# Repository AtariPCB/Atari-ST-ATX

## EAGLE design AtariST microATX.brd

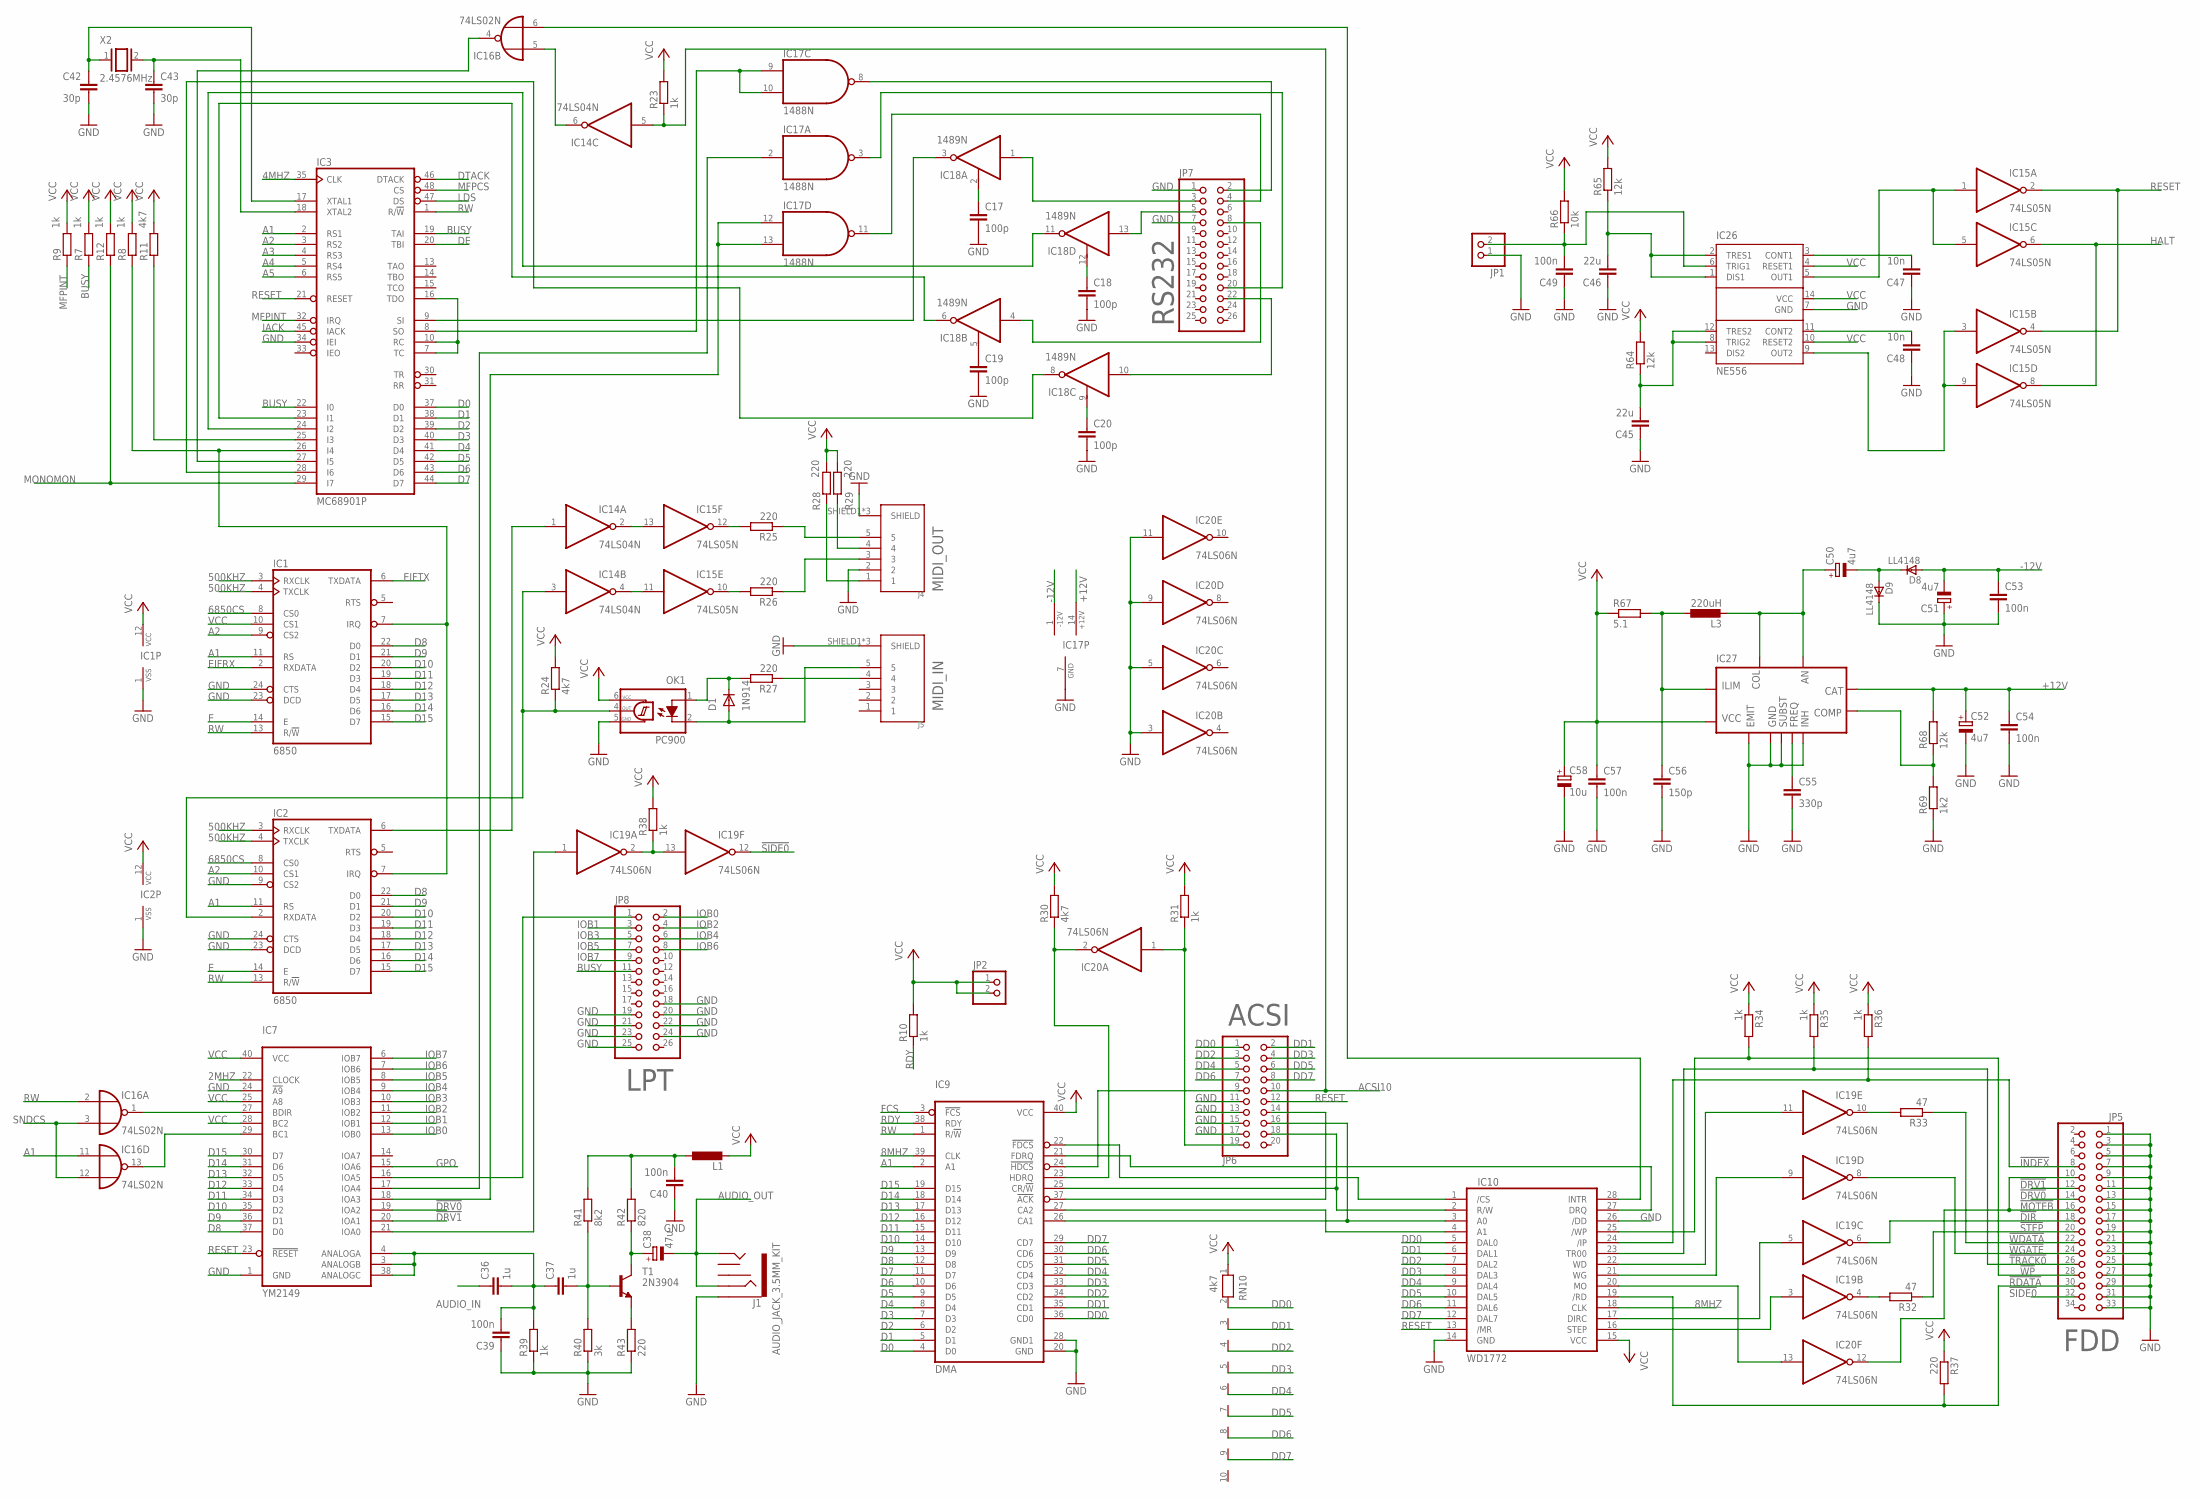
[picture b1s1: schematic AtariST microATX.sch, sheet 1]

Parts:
C17, C18, C19, C20: 100p; C0805
C36, C37: 1u; C0805
C38: 47u; E2-5
C39, C40, C49, C53, C54, C57: 100n; C0805
C42, C43: 30p; C0805
C45, C46: 22u; C1206
C47, C48: 10n; C0805
C50, C51, C52: 4u7; E2-5
C55: 330p; C0805
C56: 150p; C0805
C58: 10u; E2-5
D1: 1N914; DO35-10
D8, D9: LL4148; SOD80_DO213AA_MINIMELF
IC1, IC2: 6850; DIL24
IC3: MC68901P; DIL48
IC7: YM2149; DIL40
IC9: DMA; DIL40
IC10: WD1772; DIL28
IC14: 74LS04N; DIL14
IC15: 74LS05N; DIL14
IC16: 74LS02N; DIL14
IC17: 1488N; DIL14
IC18: 1489N; DIL14
IC19, IC20: 74LS06N; DIL14
IC26: NE556; DIL14
IC27: TL497; DIL14
J1: AUDIO_JACK_3.5MM_KIT; AUDIO-JACK-KIT
J4: MIDI_OUT; DIN5
J5: MIDI_IN; DIN5
JP1, JP2: PINHD-1X2; 1X02
JP5: PINHD-2X17; 2X17
JP6: PINHD-2X10; 2X10
JP7: RS232; 2X13
JP8: LPT; 2X13
L1: L-EU0204/7; 0204/7
L3: 220uH; 0204/7
OK1: PC900; DIL06
R7, R8, R9, R10, R12, R23, R31, R34, R35, R36, R38, R39: 1k; R0805
R11, R24, R30: 4k7; R0805
R25, R26, R27, R28, R29, R37, R43: 220; R0805
R32, R33: 47; 0204/5
R40: 3k; R0805
R41: 8k2; R0805
R42: 820; R0805
R64, R65, R68: 12k; R0805
R66: 10k; R0805
R67: 5.1; 0204/7
R69: 1k2; R0805
RN10: 4k7; RN-10
T1: 2N3904; TO92
X2: 2.4576MHz; QS

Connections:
2: J5.2
2MHZ: IC7.22 (CLOCK); also elsewhere on the board
4MHZ: IC3.35 (CLK); also elsewhere on the board
8MHZ: IC9.39 (CLK), IC10.18 (CLK); also elsewhere on the board
500KHZ: IC1.3 (RXCLK), IC1.4 (TXCLK), IC2.3 (RXCLK), IC2.4 (TXCLK); also elsewhere on the board
6850CS: IC1.8 (CS0), IC2.8 (CS0); also elsewhere on the board
!DIR: IC19.6 (O), JP5.18
!DRV0: IC7.19 (IOA2), JP5.14
!DRV1: IC7.20 (IOA1), JP5.12
!INDEX: IC10.24 (/IP), JP5.8, R36.2
!MOTEB: IC20.12 (O), JP5.10, JP5.16
!RDATA: IC10.19 (/RD), JP5.30, R37.2
!SIDE0: IC19.12 (O), JP5.32
!STEP: JP5.20, R32.1
!TRACK0: IC10.23 (TR00), JP5.26, R35.2
!WDATA: JP5.22, R33.1
!WGATE: IC19.8 (O), JP5.24
!WP: IC10.25 (/WP), JP5.28, R34.2
+12V: C52.+, C54.1, IC17.14 (+12V), IC27.6 (CAT), R68.2; also elsewhere on the board
-12V: C51.-, C53.1, D8.A, IC17.1 (-12V)
A1: IC1.11 (RS), IC2.11 (RS), IC3.2 (RS1), IC9.2 (A1), IC16.11 (I0); also elsewhere on the board
A2: IC1.9 (CS2), IC2.10 (CS1), IC3.3 (RS2); also elsewhere on the board
A3: IC3.4 (RS3); also elsewhere on the board
A4: IC3.5 (RS4); also elsewhere on the board
A5: IC3.6 (RS5); also elsewhere on the board
ACSI10: IC14.5 (I), JP6.10, R23.1; also elsewhere on the board
AUDIO_IN: C36.1; also elsewhere on the board
AUDIO_OUT: C38.-, J1.RING, J1.TIP; also elsewhere on the board
BUSY: IC3.19 (TAI), IC3.22 (I0), JP8.11, R7.1
D0: IC3.37 (D0), IC9.4 (D0); also elsewhere on the board
D1: IC3.38 (D1), IC9.5 (D1); also elsewhere on the board
D2: IC3.39 (D2), IC9.6 (D2); also elsewhere on the board
D3: IC3.40 (D3), IC9.7 (D3); also elsewhere on the board
D4: IC3.41 (D4), IC9.8 (D4); also elsewhere on the board
D5: IC3.42 (D5), IC9.9 (D5); also elsewhere on the board
D6: IC3.43 (D6), IC9.10 (D6); also elsewhere on the board
D7: IC3.44 (D7), IC9.11 (D7); also elsewhere on the board
D8: IC1.22 (D0), IC2.22 (D0), IC7.37 (D0), IC9.12 (D8); also elsewhere on the board
D9: IC1.21 (D1), IC2.21 (D1), IC7.36 (D1), IC9.13 (D9); also elsewhere on the board
D10: IC1.20 (D2), IC2.20 (D2), IC7.35 (D2), IC9.14 (D10); also elsewhere on the board
D11: IC1.19 (D3), IC2.19 (D3), IC7.34 (D3), IC9.15 (D11); also elsewhere on the board
D12: IC1.18 (D4), IC2.18 (D4), IC7.33 (D4), IC9.16 (D12); also elsewhere on the board
D13: IC1.17 (D5), IC2.17 (D5), IC7.32 (D5), IC9.17 (D13); also elsewhere on the board
D14: IC1.16 (D6), IC2.16 (D6), IC7.31 (D6), IC9.18 (D14); also elsewhere on the board
D15: IC1.15 (D7), IC2.15 (D7), IC7.30 (D7), IC9.19 (D15); also elsewhere on the board
DD0: IC9.36 (CD0), IC10.5 (DAL0), JP6.1, RN10.2
DD1: IC9.35 (CD1), IC10.6 (DAL1), JP6.2, RN10.3
DD2: IC9.34 (CD2), IC10.7 (DAL2), JP6.3, RN10.4
DD3: IC9.33 (CD3), IC10.8 (DAL3), JP6.4, RN10.5
DD4: IC9.32 (CD4), IC10.9 (DAL4), JP6.5, RN10.6
DD5: IC9.31 (CD5), IC10.10 (DAL5), JP6.6, RN10.7
DD6: IC9.30 (CD6), IC10.11 (DAL6), JP6.7, RN10.8
DD7: IC9.29 (CD7), IC10.12 (DAL7), JP6.8, RN10.9
DE: IC3.20 (TBI); also elsewhere on the board
DTACK: IC3.46 (DTACK); also elsewhere on the board
E: IC1.14 (E), IC2.14 (E); also elsewhere on the board
EIFRX: IC1.2 (RXDATA); also elsewhere on the board
EIFTX: IC1.6 (TXDATA); also elsewhere on the board
FCS: IC9.3 (!FCS); also elsewhere on the board
GND: C17.2, C18.2, C19.2, C20.2, C39.1, C40.1, C42.2, C43.2, C45.1, C46.1, C47.1, C48.1, C49.1, C51.+, C52.-, C53.2, C54.2, C55.2, C56.2, C57.2, C58.-, D9.C, IC1.1 (VSS), IC1.23 (DCD), IC1.24 (CTS), IC2.1 (VSS), IC2.9 (CS2), IC2.23 (DCD), IC2.24 (CTS), IC3.34 (IEI), IC3.36 (GND), IC7.1 (GND), IC7.24 (!A9), IC9.20 (GND), IC9.28 (GND1), IC10.14 (GND), IC10.26 (/DD), IC14.7 (GND), IC15.7 (GND), IC16.7 (GND), IC17.7 (GND), IC18.7 (GND), IC19.7 (GND), IC20.3 (I), IC20.5 (I), IC20.7 (GND), IC20.9 (I), IC20.11 (I), IC26.7 (GND), IC27.2 (INH), IC27.4 (SUBST), IC27.5 (GND), IC27.8 (EMIT), J1.SLEEVE, J4.2, J4.SHIELD1 (SHIELD), J4.SHIELD2 (SHIELD), J4.SHIELD3 (SHIELD), J5.SHIELD1 (SHIELD), J5.SHIELD2 (SHIELD), J5.SHIELD3 (SHIELD), JP1.1, JP5.1, JP5.3, JP5.5, JP5.7, JP5.9, JP5.11, JP5.13, JP5.15, JP5.17, JP5.19, JP5.21, JP5.23, JP5.25, JP5.27, JP5.29, JP5.31, JP5.33, JP6.11, JP6.13, JP6.15, JP6.17, JP7.1, JP7.7, JP8.18, JP8.19, JP8.20, JP8.21, JP8.22, JP8.23, JP8.24, JP8.25, OK1.5 (GND), R39.1, R40.1, R43.1, R69.1; also elsewhere on the board
GPO: IC7.15 (IOA6); also elsewhere on the board
HALT: IC15.6 (O), IC15.8 (O); also elsewhere on the board
IACK: IC3.45 (IACK); also elsewhere on the board
IOB0: IC7.13 (IOB0), JP8.2
IOB1: IC7.12 (IOB1), JP8.3
IOB2: IC7.11 (IOB2), JP8.4
IOB3: IC7.10 (IOB3), JP8.5
IOB4: IC7.9 (IOB4), JP8.6
IOB5: IC7.8 (IOB5), JP8.7
IOB6: IC7.7 (IOB6), JP8.8
IOB7: IC7.6 (IOB7), JP8.9
LDS: IC3.47 (DS); also elsewhere on the board
MFPCS: IC3.48 (CS); also elsewhere on the board
MFPINT: IC3.32 (IRQ), R9.1; also elsewhere on the board
MONOMON: IC3.29 (I7), R12.1; also elsewhere on the board
unnamed: C48.2, IC26.11 (CONT2)
unnamed: IC7.16 (IOA5), JP8.1
unnamed: IC7.27 (BDIR), IC16.1 (O)
unnamed: IC7.29 (BC1), IC16.13 (O)
unnamed: IC1.7 (IRQ), IC2.7 (IRQ), IC3.26 (I4), R8.1
unnamed: IC3.7 (TC), IC3.10 (RC), IC3.16 (TDO)
unnamed: IC3.9 (SI), IC18.3 (O)
unnamed: IC3.8 (SO), IC17.9 (I0), IC17.10 (I1)
unnamed: IC3.25 (I3), R11.1
unnamed: IC17.8 (O), JP7.2
unnamed: IC18.1 (I), JP7.3
unnamed: IC17.11 (O), JP7.4
unnamed: IC18.13 (I), JP7.5
unnamed: IC18.4 (I), JP7.8
unnamed: IC18.10 (I), JP7.22
unnamed: IC17.3 (O), JP7.20
unnamed: C19.1, IC18.5 (RC)
unnamed: C20.1, IC18.9 (RC)
unnamed: C18.1, IC18.12 (RC)
unnamed: C17.1, IC18.2 (RC)
unnamed: IC3.24 (I2), IC18.11 (O)
unnamed: IC3.23 (I1), IC18.6 (O)
unnamed: IC3.28 (I6), IC18.8 (O)
unnamed: IC7.17 (IOA4), IC17.2 (I)
unnamed: IC7.18 (IOA3), IC17.12 (I0), IC17.13 (I1)
unnamed: IC10.28 (INTR), IC16.6 (I1)
unnamed: IC14.6 (O), IC16.5 (I0)
unnamed: IC3.27 (I5), IC16.4 (O)
unnamed: IC2.6 (TXDATA), IC14.1 (I)
unnamed: IC2.2 (RXDATA), IC14.3 (I), OK1.4 (OUT), R24.1
unnamed: IC14.2 (O), IC15.13 (I)
unnamed: IC14.4 (O), IC15.11 (I)
unnamed: J4.1, R28.1
unnamed: J4.4, R29.1
unnamed: IC9.26 (CA1), IC10.3 (A0), JP6.16
unnamed: J4.5, R25.1
unnamed: J4.3, R26.1
unnamed: IC15.10 (O), R26.2
unnamed: IC15.12 (O), R25.2
unnamed: J5.4, R27.1
unnamed: D1.C, OK1.1 (A), R27.2
unnamed: D1.A, J5.5, OK1.2 (C)
unnamed: IC9.27 (CA2), IC10.4 (A1)
unnamed: IC9.25 (CR/!W), IC10.2 (R/W), JP6.18
unnamed: IC9.22 (!FDCS), IC10.1 (/CS)
unnamed: IC9.21 (FDRQ), IC10.27 (DRQ)
unnamed: IC9.24 (!HDCS), JP6.9
unnamed: IC9.37 (!ACK), JP6.14
unnamed: IC20.1 (I), JP6.19, R31.1
unnamed: IC9.23 (HDRQ), IC20.2 (O), R30.1
unnamed: IC10.17 (DIRC), IC19.5 (I)
unnamed: IC19.4 (O), R32.2
unnamed: IC10.20 (MO), IC20.13 (I)
unnamed: IC7.21 (IOA0), IC19.1 (I)
unnamed: IC19.2 (O), IC19.13 (I), R38.1
unnamed: C36.2, C37.1, C39.2, IC7.3 (ANALOGB), IC7.4 (ANALOGA), IC7.38 (ANALOGC), R39.2
unnamed: IC10.16 (STEP), IC19.3 (I)
unnamed: IC10.22 (WD), IC19.11 (I)
unnamed: IC10.21 (WG), IC19.9 (I)
unnamed: IC19.10 (O), R33.2
unnamed: C37.2, R40.2, R41.1, T1.2 (B)
unnamed: C38.+, R42.1, T1.1 (C)
unnamed: R43.2, T1.3 (E)
unnamed: C42.1, IC3.17 (XTAL1), X2.1
unnamed: C43.1, IC3.18 (XTAL2), X2.2
unnamed: C40.2, L1.1, R41.2, R42.2
unnamed: C47.2, IC26.3 (CONT1)
unnamed: C45.2, IC26.8 (TRIG2), IC26.12 (TRES2), R64.1
unnamed: C56.1, IC27.13 (ILIM), L3.1, R67.2
unnamed: C46.2, IC26.1 (DIS1), IC26.2 (TRES1), R65.1
unnamed: C50.+, IC27.7 (AN), IC27.10 (COL), L3.2
unnamed: C49.2, IC26.6 (TRIG1), JP1.2, R66.1
unnamed: C50.-, D8.C, D9.A
unnamed: IC15.1 (I), IC15.5 (I), IC26.5 (OUT1)
unnamed: IC15.3 (I), IC15.9 (I), IC26.9 (OUT2)
unnamed: IC27.1 (COMP), R68.1, R69.2
unnamed: C55.1, IC27.3 (FREQ)
RDY: IC9.38 (RDY), R10.1; also elsewhere on the board
RESET: IC3.21 (RESET), IC7.23 (!RESET), IC10.13 (/MR), IC15.2 (O), IC15.4 (O), JP6.12; also elsewhere on the board
RW: IC1.13 (R/!W), IC2.13 (R/!W), IC3.1 (R/!W), IC9.1 (R/!W), IC16.2 (I0); also elsewhere on the board
SNDCS: IC16.3 (I1), IC16.12 (I1); also elsewhere on the board
VCC: C57.1, C58.+, IC1.10 (CS1), IC1.12 (VCC), IC2.12 (VCC), IC3.11 (VCC), IC7.25 (A8), IC7.28 (BC2), IC7.40 (VCC), IC9.40 (VCC), IC10.15 (VCC), IC14.14 (VCC), IC15.14 (VCC), IC16.14 (VCC), IC18.14 (VCC), IC19.14 (VCC), IC20.14 (VCC), IC26.4 (RESET1), IC26.10 (RESET2), IC26.14 (VCC), IC27.14 (VCC), JP2.1, JP2.2, L1.2, OK1.6 (VCC), R7.2, R8.2, R9.2, R10.2, R11.2, R12.2, R23.2, R24.2, R28.2, R29.2, R30.2, R31.2, R34.1, R35.1, R36.1, R37.1, R38.2, R64.2, R65.2, R66.2, R67.1, RN10.1; also elsewhere on the board

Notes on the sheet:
FDD
ACSI

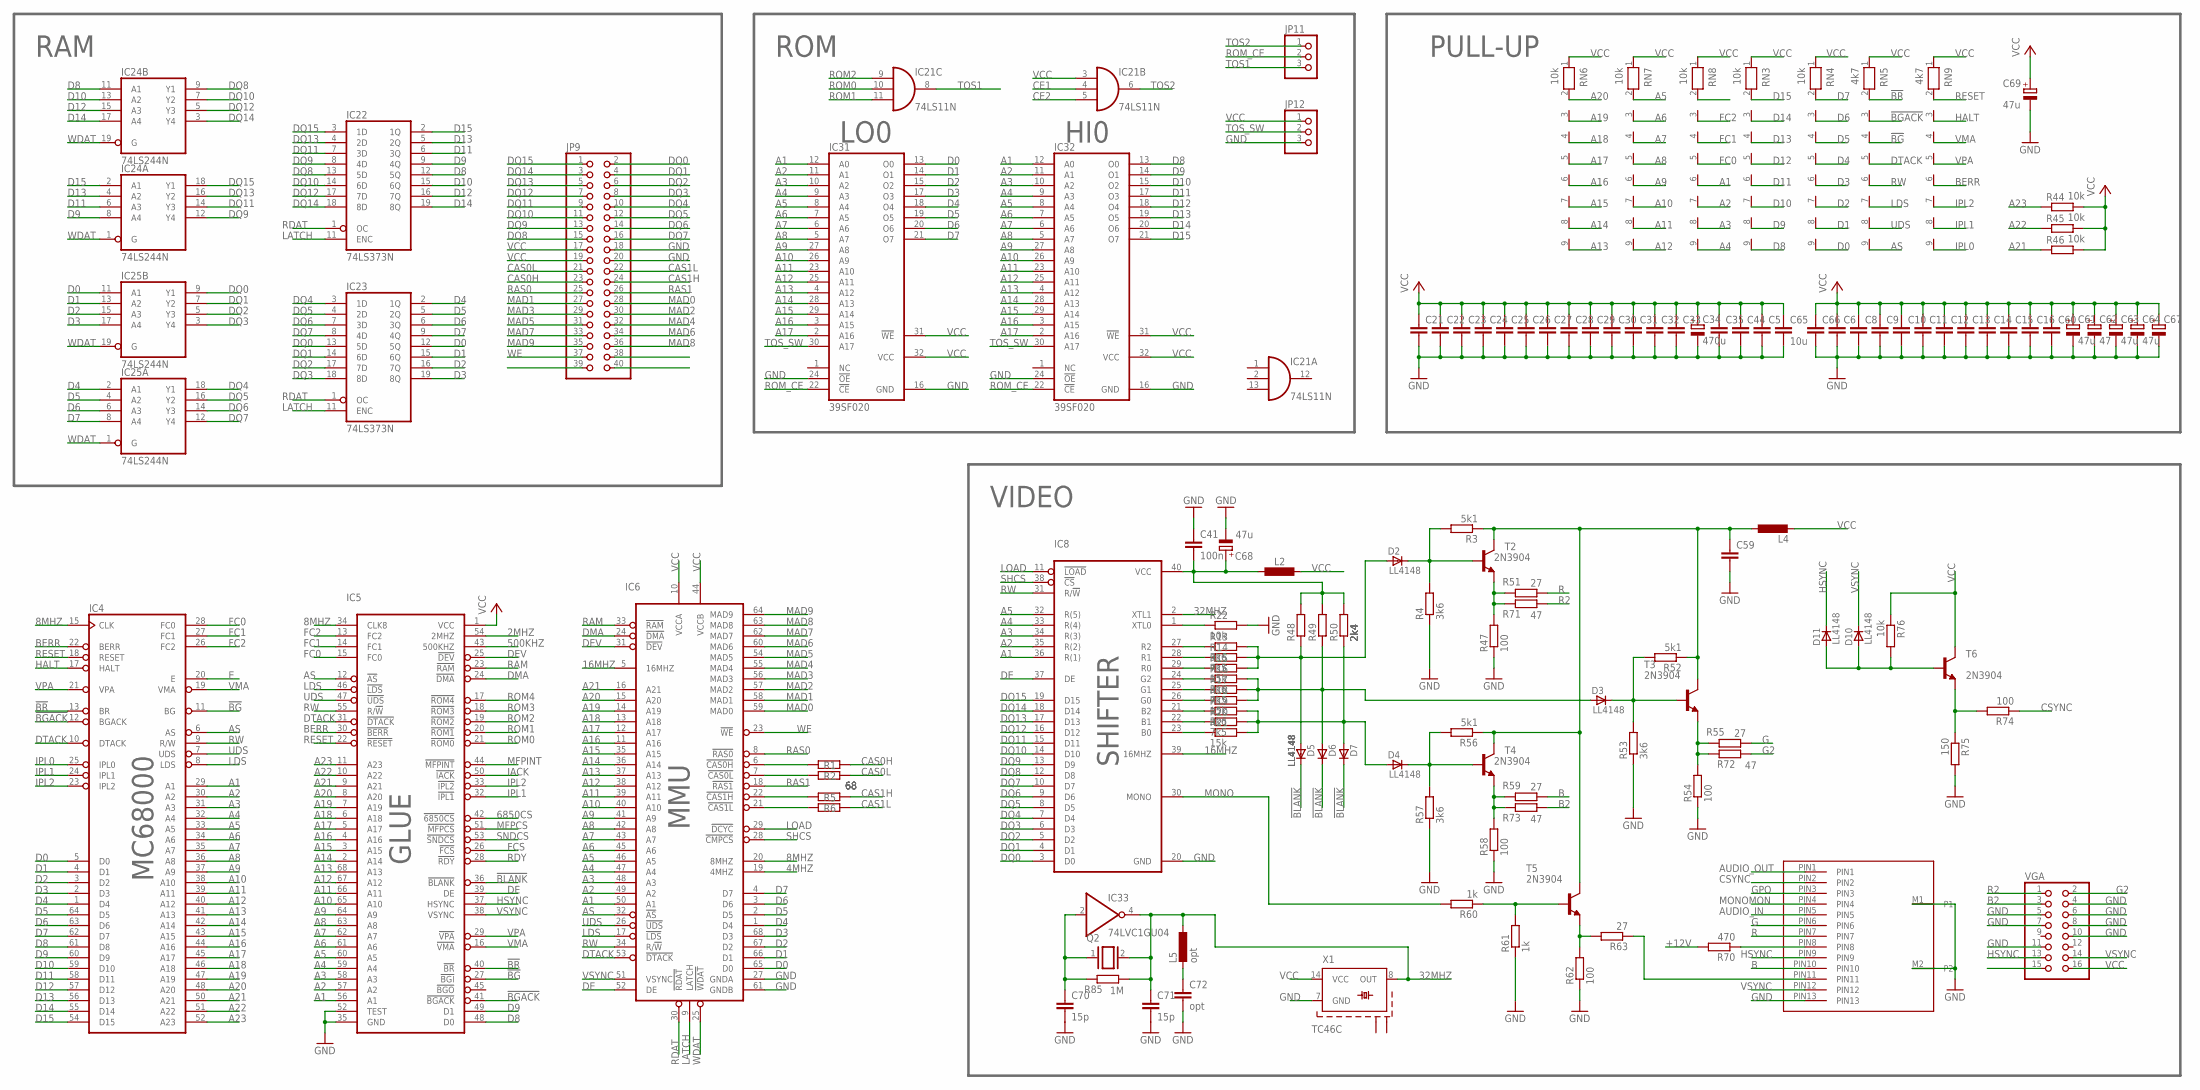
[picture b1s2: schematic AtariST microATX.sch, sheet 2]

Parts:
C5, C16, C25, C28, C29, C30, C32, C33, C59: C-EU050-025X075; C050-025X075
C6, C8, C9, C10, C11, C12, C13, C14, C15, C21, C22, C23, C24, C27, C31, C35, C44, C60, C66: C-EUC0805; C0805
C26: C-EU075-032X103; C075-032X103
C34: 470u; E3,5-8
C41: 100n; C050-025X075
C61, C63, C64: 47u; E2-5
C62: 47; E2-5
C65: 10u; C0805
C67: CPOL-EUC/6032-28R; C/6032-28R
C68, C69: 47u; E2,5-5
C70, C71: 15p; C0805
C72: opt; C0805
D2, D3, D4, D5, D6, D7, D10, D11: LL4148; SOD80_DO213AA_MINIMELF
IC4: MC68000; DIL64
IC5: GLUE; PLCC68
IC6: MMU; PLCC68
IC8: SHIFTER; DIL40
IC21: 74LS11N; DIL14
IC22, IC23: 74LS373N; DIL20
IC24, IC25: 74LS244N; DIL20
IC31, IC32: 39SF020; DIL32
IC33: 74LVC1GU04; SOT23-5
JP9: PINHD-2X20; 2X20
JP11, JP12: PINHD-1X3; 1X03
L2, L4: L-EU0204/7; 0204/7
L5: opt; 0204/7
Q2: XTAL/S; QS
R1, R2, R5, R6: 68; R0805
R3, R52, R56: 5k1; R0805
R4, R53, R57: 3k6; R0805
R13, R16, R19: 3k6; 0204/5
R14, R17, R20: 7k5; 0204/5
R15, R18, R21: 15k; 0204/5
R22, R44, R45, R46, R76: 10k; R0805
R47, R54, R58, R62, R74: 100; R0805
R48, R49, R50: 2k4; R0805
R51, R55, R59, R63: 27; R0805
R60, R61: 1k; R0805
R70: 470; R0805
R71, R72, R73: 47; R0805
R75: 150; R0805
R85: 1M; R0805
RN3, RN4, RN6, RN7, RN8: 10k; RN-9
RN5, RN9: 4k7; RN-9
T2, T3, T4, T5, T6: 2N3904; TO92
U$6: Monitor; DIN-13
VGA: PINHD-2X8; 2X08
X1: TC46C; TC46

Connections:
2MHZ: IC5.54 (2MHZ); also elsewhere on the board
4MHZ: IC6.19 (4MHZ); also elsewhere on the board
8MHZ: IC4.15 (CLK), IC5.34 (CLK8), IC6.20 (8MHZ); also elsewhere on the board
16MHZ: IC6.5 (16MHZ), IC8.39 (16MHZ)
32MHZ: C71.1, IC8.2 (XTL1), IC33.4 (O), L5.1, Q2.2, R85.1, X1.8 (OUT)
500KHZ: IC5.43 (500KHZ); also elsewhere on the board
6850CS: IC5.42 (!6850CS); also elsewhere on the board
!BG: IC4.11 (BG), IC5.27 (!BGI), RN5.4
!BGACK: IC4.12 (BGACK), IC5.41 (!BGACK), RN5.3
!BLANK: D5.C, D6.C, D7.C, IC5.36 (!BLANK)
!BR: IC4.13 (BR), IC5.40 (!BR), RN5.2
+12V: R70.2; also elsewhere on the board
A1: IC4.29 (A1), IC5.56 (A1), IC6.50 (A1), IC8.36 (R(1)), IC31.12 (A0), IC32.12 (A0), RN8.6; also elsewhere on the board
A2: IC4.30 (A2), IC5.57 (A2), IC6.49 (A2), IC8.35 (R(2)), IC31.11 (A1), IC32.11 (A1), RN8.7; also elsewhere on the board
A3: IC4.31 (A3), IC5.58 (A3), IC6.48 (A3), IC8.34 (R(3)), IC31.10 (A2), IC32.10 (A2), RN8.8; also elsewhere on the board
A4: IC4.32 (A4), IC5.59 (A4), IC6.47 (A4), IC8.33 (R(4)), IC31.9 (A3), IC32.9 (A3), RN8.9; also elsewhere on the board
A5: IC4.33 (A5), IC5.60 (A5), IC6.46 (A5), IC8.32 (R(5)), IC31.8 (A4), IC32.8 (A4), RN7.2; also elsewhere on the board
A6: IC4.34 (A6), IC5.61 (A6), IC6.45 (A6), IC31.7 (A5), IC32.7 (A5), RN7.3; also elsewhere on the board
A7: IC4.35 (A7), IC5.62 (A7), IC6.43 (A7), IC31.6 (A6), IC32.6 (A6), RN7.4; also elsewhere on the board
A8: IC4.36 (A8), IC5.63 (A8), IC6.42 (A8), IC31.5 (A7), IC32.5 (A7), RN7.5; also elsewhere on the board
A9: IC4.37 (A9), IC5.64 (A9), IC6.41 (A9), IC31.27 (A8), IC32.27 (A8), RN7.6; also elsewhere on the board
A10: IC4.38 (A10), IC5.65 (A10), IC6.40 (A10), IC31.26 (A9), IC32.26 (A9), RN7.7; also elsewhere on the board
A11: IC4.39 (A11), IC5.66 (A11), IC6.39 (A11), IC31.23 (A10), IC32.23 (A10), RN7.8; also elsewhere on the board
A12: IC4.40 (A12), IC5.67 (A12), IC6.38 (A12), IC31.25 (A11), IC32.25 (A11), RN7.9; also elsewhere on the board
A13: IC4.41 (A13), IC5.68 (A13), IC6.37 (A13), IC31.4 (A12), IC32.4 (A12), RN6.9; also elsewhere on the board
A14: IC4.42 (A14), IC5.2 (A14), IC6.36 (A14), IC31.28 (A13), IC32.28 (A13), RN6.8; also elsewhere on the board
A15: IC4.43 (A15), IC5.3 (A15), IC6.35 (A15), IC31.29 (A14), IC32.29 (A14), RN6.7; also elsewhere on the board
A16: IC4.44 (A16), IC5.4 (A16), IC6.11 (A16), IC31.3 (A15), IC32.3 (A15), RN6.6; also elsewhere on the board
A17: IC4.45 (A17), IC5.5 (A17), IC6.12 (A17), IC31.2 (A16), IC32.2 (A16), RN6.5; also elsewhere on the board
A18: IC4.46 (A18), IC5.6 (A18), IC6.13 (A18), RN6.4; also elsewhere on the board
A19: IC4.47 (A19), IC5.7 (A19), IC6.14 (A19), RN6.3; also elsewhere on the board
A20: IC4.48 (A20), IC5.8 (A20), IC6.15 (A20), RN6.2; also elsewhere on the board
A21: IC4.50 (A21), IC5.9 (A21), IC6.16 (A21), R46.1; also elsewhere on the board
A22: IC4.51 (A22), IC5.10 (A22), R45.1; also elsewhere on the board
A23: IC4.52 (A23), IC5.11 (A23), R44.1; also elsewhere on the board
AS: IC4.6 (AS), IC5.12 (!AS), IC6.32 (!AS), RN5.9; also elsewhere on the board
AUDIO_IN: U$6.PIN5; also elsewhere on the board
AUDIO_OUT: U$6.PIN1; also elsewhere on the board
B: R59.1, U$6.PIN10
B2: R73.1, VGA.3
BERR: IC4.22 (BERR), IC5.30 (!BERR), RN9.6
CAS0H: JP9.23, R1.2
CAS0L: JP9.21, R2.2
CAS1H: JP9.24, R5.2
CAS1L: JP9.22, R6.2
CE1: IC21.4 (I1); also elsewhere on the board
CE2: IC21.5 (I2); also elsewhere on the board
CSYNC: R74.1, U$6.PIN2
D0: IC4.5 (D0), IC6.65 (D0), IC23.12 (5Q), IC25.11 (A1), IC31.13 (O0), RN4.9; also elsewhere on the board
D1: IC4.4 (D1), IC6.66 (D1), IC23.15 (6Q), IC25.13 (A2), IC31.14 (O1), RN4.8; also elsewhere on the board
D2: IC4.3 (D2), IC6.67 (D2), IC23.16 (7Q), IC25.15 (A3), IC31.15 (O2), RN4.7; also elsewhere on the board
D3: IC4.2 (D3), IC6.68 (D3), IC23.19 (8Q), IC25.17 (A4), IC31.17 (O3), RN4.6; also elsewhere on the board
D4: IC4.1 (D4), IC6.1 (D4), IC23.2 (1Q), IC25.2 (A1), IC31.18 (O4), RN4.5; also elsewhere on the board
D5: IC4.64 (D5), IC6.2 (D5), IC23.5 (2Q), IC25.4 (A2), IC31.19 (O5), RN4.4; also elsewhere on the board
D6: IC4.63 (D6), IC6.3 (D6), IC23.6 (3Q), IC25.6 (A3), IC31.20 (O6), RN4.3; also elsewhere on the board
D7: IC4.62 (D7), IC6.4 (D7), IC23.9 (4Q), IC25.8 (A4), IC31.21 (O7), RN4.2; also elsewhere on the board
D8: IC4.61 (D8), IC5.48 (D0), IC22.12 (5Q), IC24.11 (A1), IC32.13 (O0), RN3.9; also elsewhere on the board
D9: IC4.60 (D9), IC5.49 (D1), IC22.9 (4Q), IC24.8 (A4), IC32.14 (O1), RN3.8; also elsewhere on the board
D10: IC4.59 (D10), IC22.15 (6Q), IC24.13 (A2), IC32.15 (O2), RN3.7; also elsewhere on the board
D11: IC4.58 (D11), IC22.6 (3Q), IC24.6 (A3), IC32.17 (O3), RN3.6; also elsewhere on the board
D12: IC4.57 (D12), IC22.16 (7Q), IC24.15 (A3), IC32.18 (O4), RN3.5; also elsewhere on the board
D13: IC4.56 (D13), IC22.5 (2Q), IC24.4 (A2), IC32.19 (O5), RN3.4; also elsewhere on the board
D14: IC4.55 (D14), IC22.19 (8Q), IC24.17 (A4), IC32.20 (O6), RN3.3; also elsewhere on the board
D15: IC4.54 (D15), IC22.2 (1Q), IC24.2 (A1), IC32.21 (O7), RN3.2; also elsewhere on the board
DE: IC5.39 (DE), IC6.52 (DE), IC8.37 (DE); also elsewhere on the board
DEV: IC5.25 (!DEV), IC6.31 (!DEV)
DMA: IC5.24 (!DMA), IC6.24 (!DMA)
DQ0: IC8.3 (D0), IC23.13 (5D), IC25.9 (Y1), JP9.2
DQ1: IC8.4 (D1), IC23.14 (6D), IC25.7 (Y2), JP9.4
DQ2: IC8.5 (D2), IC23.17 (7D), IC25.5 (Y3), JP9.6
DQ3: IC8.6 (D3), IC23.18 (8D), IC25.3 (Y4), JP9.8
DQ4: IC8.7 (D4), IC23.3 (1D), IC25.18 (Y1), JP9.10
DQ5: IC8.8 (D5), IC23.4 (2D), IC25.16 (Y2), JP9.12
DQ6: IC8.9 (D6), IC23.7 (3D), IC25.14 (Y3), JP9.14
DQ7: IC8.10 (D7), IC23.8 (4D), IC25.12 (Y4), JP9.16
DQ8: IC8.12 (D8), IC22.13 (5D), IC24.9 (Y1), JP9.15
DQ9: IC8.13 (D9), IC22.8 (4D), IC24.12 (Y4), JP9.13
DQ10: IC8.14 (D10), IC22.14 (6D), IC24.7 (Y2), JP9.11
DQ11: IC8.15 (D11), IC22.7 (3D), IC24.14 (Y3), JP9.9
DQ12: IC8.16 (D12), IC22.17 (7D), IC24.5 (Y3), JP9.7
DQ13: IC8.17 (D13), IC22.4 (2D), IC24.16 (Y2), JP9.5
DQ14: IC8.18 (D14), IC22.18 (8D), IC24.3 (Y4), JP9.3
DQ15: IC8.19 (D15), IC22.3 (1D), IC24.18 (Y1), JP9.1
DTACK: IC4.10 (DTACK), IC5.31 (!DTACK), IC6.53 (!DTACK), RN5.5; also elsewhere on the board
E: IC4.20 (E); also elsewhere on the board
FC0: IC4.28 (FC0), IC5.15 (FC0), RN8.5
FC1: IC4.27 (FC1), IC5.14 (FC1), RN8.4
FC2: IC4.26 (FC2), IC5.13 (FC2), RN8.3
FCS: IC5.26 (!FCS); also elsewhere on the board
G: R55.1, U$6.PIN6
G2: R72.1, VGA.2
GND: C5.2, C6.2, C8.2, C9.2, C10.2, C11.2, C12.2, C13.2, C14.2, C15.2, C16.2, C21.2, C22.2, C23.2, C24.2, C25.2, C26.2, C27.2, C28.2, C29.2, C30.2, C31.2, C32.2, C33.2, C34.-, C35.2, C41.1, C44.2, C59.2, C60.2, C61.-, C62.-, C63.-, C64.-, C65.2, C66.2, C67.-, C68.-, C69.-, C70.2, C71.2, C72.2, IC4.16 (GND), IC4.53 (GND), IC5.35 (GND), IC5.52 (TEST), IC6.27 (GNDA), IC6.61 (GNDB), IC8.20 (GND), IC21.7 (GND), IC22.10 (GND), IC23.10 (GND), IC24.10 (GND), IC25.10 (GND), IC31.16 (GND), IC31.24 (!OE), IC32.16 (GND), IC32.24 (!OE), IC33.3 (GND), JP9.18, JP9.20, JP12.3, R4.1, R22.2, R47.1, R53.1, R54.1, R57.1, R58.1, R61.1, R62.1, R75.2, U$6.M1 (P1), U$6.M2 (P2), U$6.PIN13, VGA.4, VGA.5, VGA.6, VGA.7, VGA.8, VGA.10, VGA.11, X1.7 (GND); also elsewhere on the board
GPO: U$6.PIN3; also elsewhere on the board
HALT: IC4.17 (HALT), RN9.3; also elsewhere on the board
HSYNC: D11.C, IC5.37 (HSYNC), U$6.PIN9, VGA.13
IACK: IC5.50 (!IACK); also elsewhere on the board
IPL0: IC4.25 (IPL0), RN9.9
IPL1: IC4.24 (IPL1), IC5.32 (!IPL1), RN9.8
IPL2: IC4.23 (IPL2), IC5.33 (!IPL2), RN9.7
LATCH: IC6.9 (LATCH), IC22.11 (ENC), IC23.11 (ENC)
LDS: IC4.8 (LDS), IC5.46 (!LDS), IC6.17 (!LDS), RN5.7; also elsewhere on the board
LOAD: IC6.29 (!DCYC), IC8.11 (!LOAD)
MAD0: IC6.59 (MAD0), JP9.28
MAD1: IC6.58 (MAD1), JP9.27
MAD2: IC6.57 (MAD2), JP9.30
MAD3: IC6.56 (MAD3), JP9.29
MAD4: IC6.55 (MAD4), JP9.32
MAD5: IC6.54 (MAD5), JP9.31
MAD6: IC6.60 (MAD6), JP9.34
MAD7: IC6.62 (MAD7), JP9.33
MAD8: IC6.63 (MAD8), JP9.36
MAD9: IC6.64 (MAD9), JP9.35
MFPCS: IC5.51 (!MFPCS); also elsewhere on the board
MFPINT: IC5.44 (!MFPINT); also elsewhere on the board
MONO: IC8.30 (MONO), R60.2
MONOMON: U$6.PIN4; also elsewhere on the board
unnamed: C41.2, C68.+, IC8.40 (VCC), L2.1, R48.2, R49.2, R50.2
unnamed: D2.C, R3.2, R4.2, T2.2 (B)
unnamed: R70.1, U$6.PIN8
unnamed: IC8.1 (XTL0), R22.1
unnamed: IC8.27 (R2), R13.1
unnamed: IC8.28 (R1), R14.1
unnamed: IC8.29 (R0), R15.1
unnamed: IC6.6 (!CAS0H), R1.1
unnamed: IC6.7 (!CAS0L), R2.1
unnamed: IC8.24 (G2), R16.1
unnamed: IC6.22 (!CAS1H), R5.1
unnamed: IC6.21 (!CAS1L), R6.1
unnamed: IC8.25 (G1), R17.1
unnamed: IC8.26 (G0), R18.1
unnamed: IC8.21 (B2), R19.1
unnamed: IC8.22 (B1), R20.1
unnamed: IC8.23 (B0), R21.1
unnamed: D2.A, D5.A, R13.2, R14.2, R15.2, R48.1
unnamed: D3.A, D6.A, R16.2, R17.2, R18.2, R49.1
unnamed: D4.A, D7.A, R19.2, R20.2, R21.2, R50.1
unnamed: R47.2, R51.2, R71.2, T2.3 (E)
unnamed: D3.C, R52.2, R53.2, T3.2 (B)
unnamed: R54.2, R55.2, R72.2, T3.3 (E)
unnamed: R63.1, U$6.PIN11
unnamed: R60.1, R61.2, T5.2 (B)
unnamed: D4.C, R56.2, R57.2, T4.2 (B)
unnamed: D10.A, D11.A, R76.2, T6.2 (B)
unnamed: R58.2, R59.2, R73.2, T4.3 (E)
unnamed: C59.1, L4.1, R3.1, R52.1, R56.1, T2.1 (C), T3.1 (C), T4.1 (C), T5.1 (C)
unnamed: R62.2, R63.2, T5.3 (E)
unnamed: R74.2, R75.1, T6.3 (E)
unnamed: C70.1, IC33.2 (I), Q2.1, R85.2
unnamed: C72.1, L5.2
R: R51.1, U$6.PIN7
R2: R71.1, VGA.1
RAM: IC5.23 (!RAM), IC6.33 (!RAM)
RAS0: IC6.8 (!RAS0), JP9.25
RAS1: IC6.18 (!RAS1), JP9.26
RDAT: IC6.30 (!RDAT), IC22.1 (OC), IC23.1 (OC)
RDY: IC5.28 (!RDY); also elsewhere on the board
RESET: IC4.18 (RESET), IC5.22 (!RESET), RN9.2; also elsewhere on the board
ROM0: IC5.21 (!ROM0), IC21.10 (I1)
ROM1: IC5.20 (!ROM1), IC21.11 (I2)
ROM2: IC5.19 (!ROM2), IC21.9 (I0); also elsewhere on the board
ROM3: IC5.18 (!ROM3); also elsewhere on the board
ROM4: IC5.17 (!ROM4); also elsewhere on the board
ROM_CE: IC31.22 (!CE), IC32.22 (!CE), JP11.2
RW: IC4.9 (R/W), IC5.55 (R/!W), IC6.34 (R/!W), IC8.31 (R/!W), RN5.6; also elsewhere on the board
SHCS: IC6.28 (!CMPCS), IC8.38 (!CS)
SNDCS: IC5.53 (!SNDCS); also elsewhere on the board
TOS1: IC21.8 (O), JP11.3
TOS2: IC21.6 (O), JP11.1
TOS_SW: IC31.30 (A17), IC32.30 (A17), JP12.2
UDS: IC4.7 (UDS), IC5.47 (!UDS), IC6.26 (!UDS), RN5.8; also elsewhere on the board
VCC: C5.1, C6.1, C8.1, C9.1, C10.1, C11.1, C12.1, C13.1, C14.1, C15.1, C16.1, C21.1, C22.1, C23.1, C24.1, C25.1, C26.1, C27.1, C28.1, C29.1, C30.1, C31.1, C32.1, C33.1, C34.+, C35.1, C44.1, C60.1, C61.+, C62.+, C63.+, C64.+, C65.1, C66.1, C67.+, C69.+, IC4.14 (VCC), IC4.49 (VCC), IC5.1 (VCC), IC6.10 (VCCA), IC6.44 (VCCB), IC21.3 (I0), IC21.14 (VCC), IC22.20 (VCC), IC23.20 (VCC), IC24.20 (VCC), IC25.20 (VCC), IC31.31 (!WE), IC31.32 (VCC), IC32.31 (!WE), IC32.32 (VCC), IC33.5 (VCC), JP9.17, JP9.19, JP12.1, L2.2, L4.2, R44.2, R45.2, R46.2, R76.1, RN3.1, RN4.1, RN5.1, RN6.1, RN7.1, RN8.1, RN9.1, T6.1 (C), VGA.16, X1.14 (VCC); also elsewhere on the board
VMA: IC4.19 (VMA), IC5.16 (!VMA), RN9.4
VPA: IC4.21 (VPA), IC5.29 (!VPA), RN9.5
VSYNC: D10.C, IC5.38 (VSYNC), IC6.51 (VSYNC), U$6.PIN12, VGA.14
WDAT: IC6.25 (!WDAT), IC24.1 (G), IC24.19 (G), IC25.1 (G), IC25.19 (G)
WE: IC6.23 (!WE), JP9.37

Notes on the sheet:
LO0
HI0
VIDEO
PULL-UP
ROM
RAM

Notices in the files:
parts and their libraries:
SparkFun-Connectors: Licensing: Creative Commons ShareAlike 4.0 International - https://creativecommons.org/licenses/by-sa/4.0
